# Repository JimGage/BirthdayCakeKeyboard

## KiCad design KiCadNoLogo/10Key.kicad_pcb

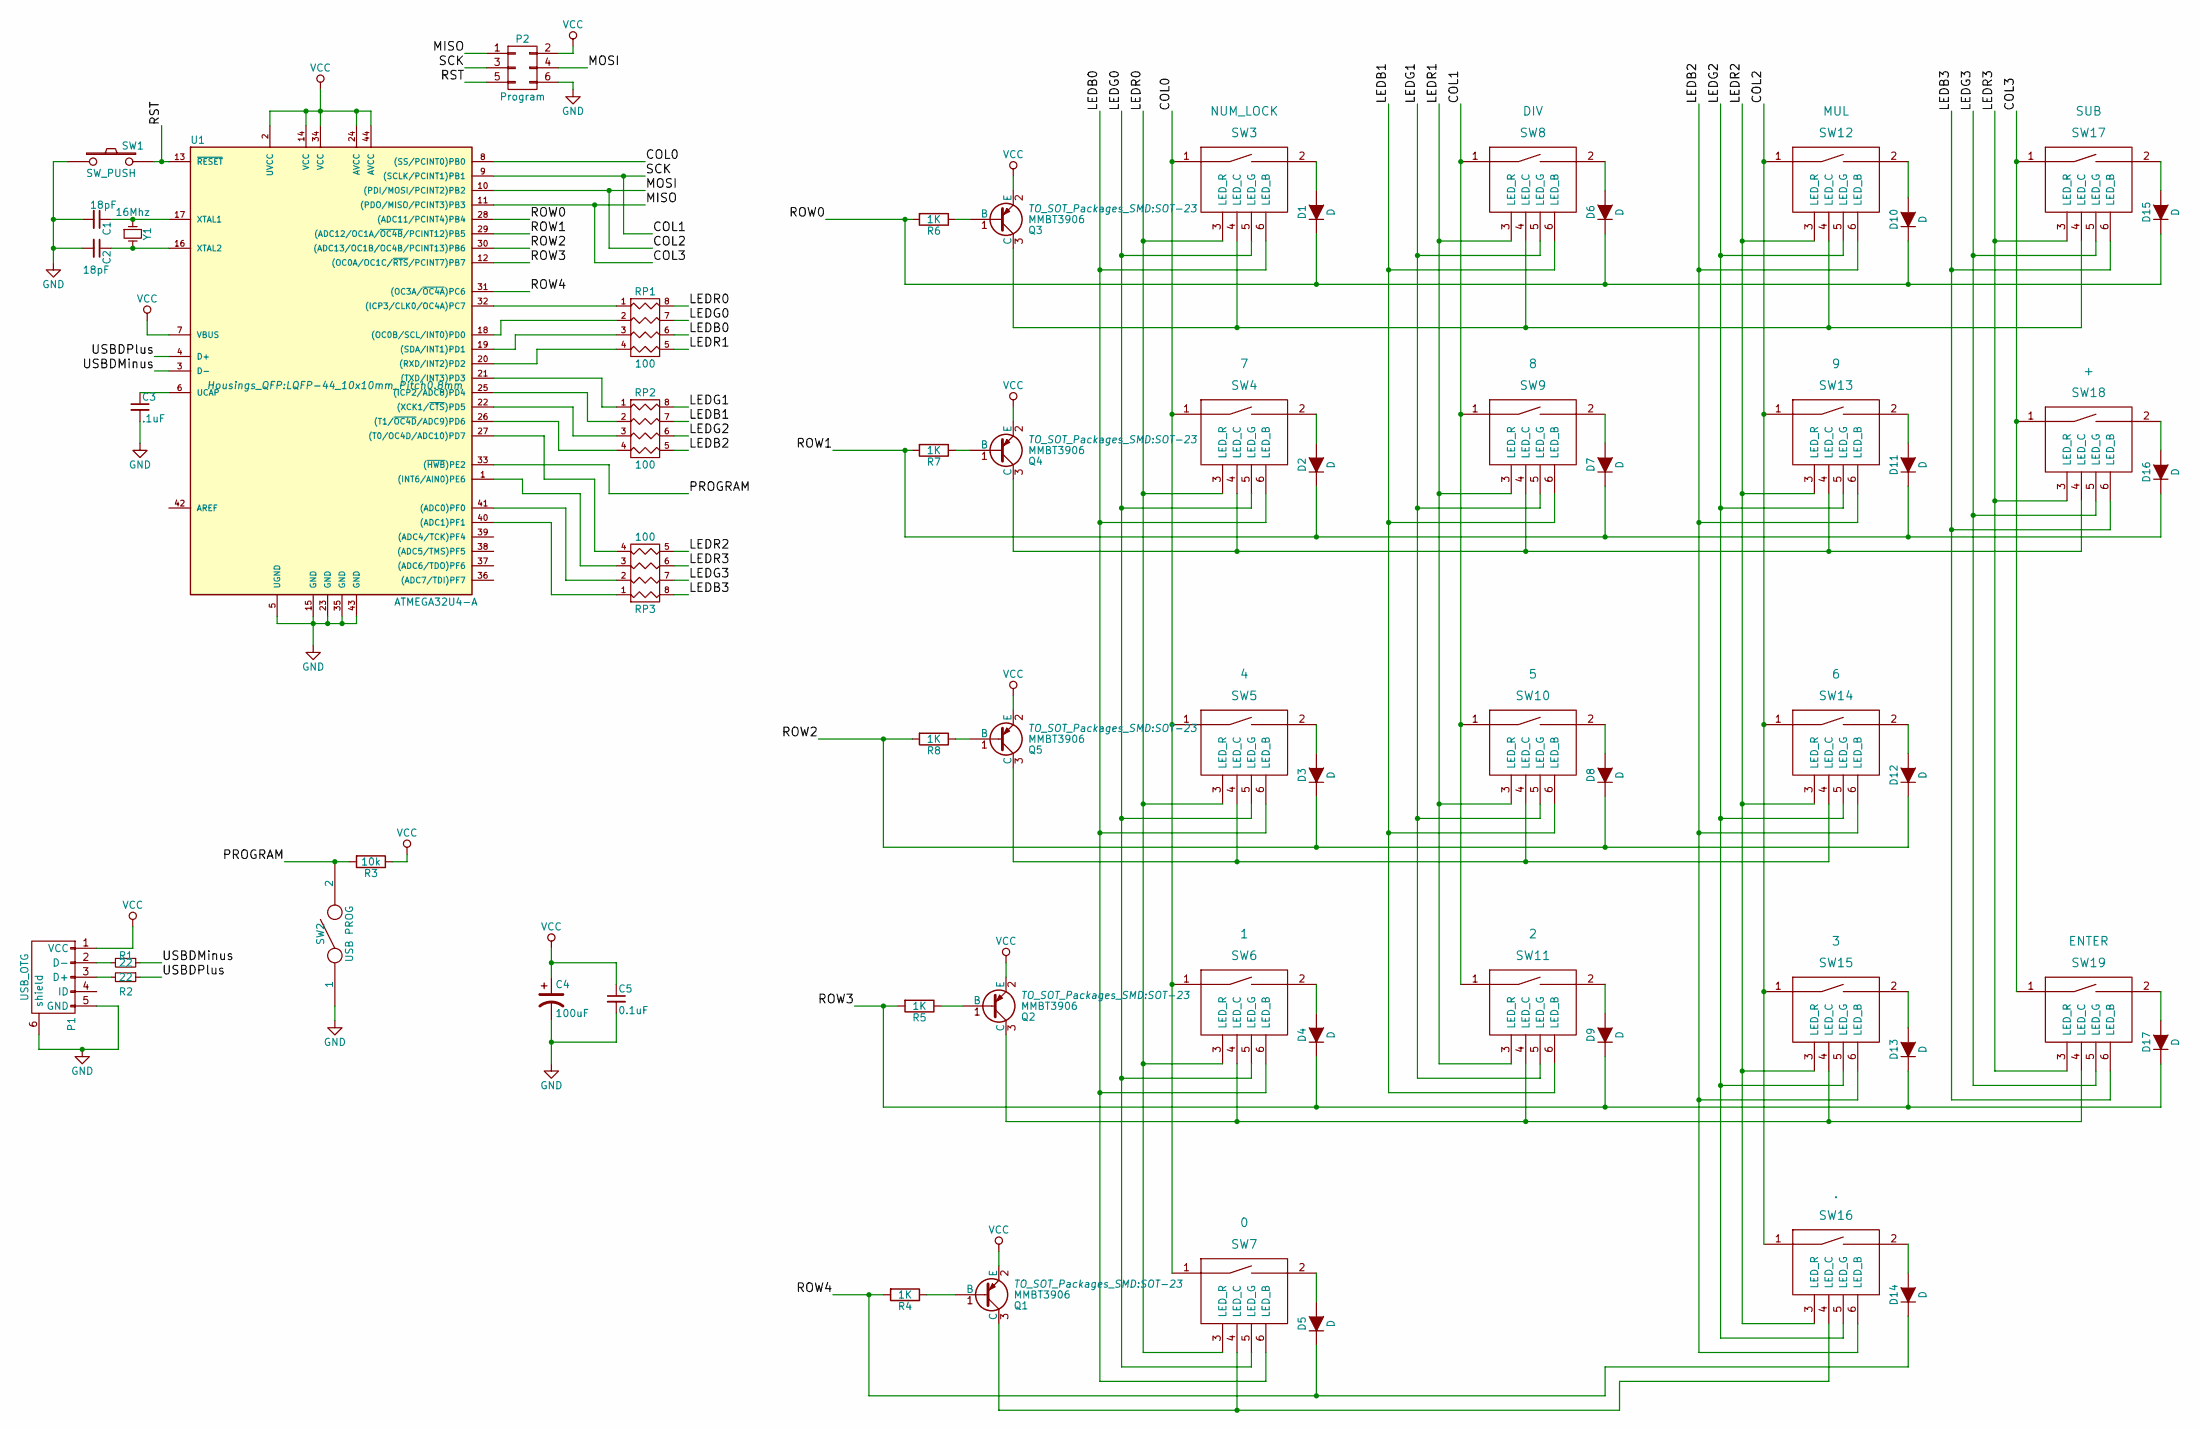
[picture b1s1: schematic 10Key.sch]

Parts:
C1, C2: 18pF; C_0603_HandSoldering
C3: .1uF; C_0603_HandSoldering
C4: 100uF; SMD-1206_Pol
C5: 0.1uF; C_0603_HandSoldering
D1, D2, D3, D4, D5, D6, D7, D8, D9, D10, D11, D12, D13, D14, D15, D16, D17: D; MiniMELF_Standard
P1: USB_OTG; USB_Micro-B
P2: Program; Pin_Header_Straight_2x03
Q1, Q2, Q3, Q4, Q5: MMBT3906; SOT-23
R1, R2: 22; R_0603_HandSoldering
R3: 10k; R_0603_HandSoldering
R4, R5, R6, R7, R8: 1K; R_0603_HandSoldering
RP1, RP2, RP3: 100; R_Array_Convex_4x1206
SW1: SW_PUSH; SW_SPST_EVQQ2
SW2: USB PROG; SW_SP3T_PCM13
SW3: NUM_LOCK; Zealios_Cherry_MX
SW4: 7; Zealios_Cherry_MX
SW5: 4; Zealios_Cherry_MX
SW6: 1; Zealios_Cherry_MX
SW7: 0; Zealios_Cherry_MX
SW8: DIV; Zealios_Cherry_MX
SW9: 8; Zealios_Cherry_MX
SW10: 5; Zealios_Cherry_MX
SW11: 2; Zealios_Cherry_MX
SW12: MUL; Zealios_Cherry_MX
SW13: 9; Zealios_Cherry_MX
SW14: 6; Zealios_Cherry_MX
SW15: 3; Zealios_Cherry_MX
SW16: .; Zealios_Cherry_MX
SW17: SUB; Zealios_Cherry_MX
SW18: +; Zealios_Cherry_MX
SW19: ENTER; Zealios_Cherry_MX
U1: ATMEGA32U4-A; LQFP-44_10x10mm_Pitch0.8mm
Y1: 16Mhz; Q_49U3HMS

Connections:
/COL0: SW3.1, SW4.1, SW5.1, SW6.1, SW7.1, U1.8 ((SS/PCINT0)PB0)
/COL1: P2.3, SW8.1, SW9.1, SW10.1, SW11.1, U1.9 ((SCLK/PCINT1)PB1)
/COL2: P2.4, SW12.1, SW13.1, SW14.1, SW15.1, SW16.1, U1.10 ((PDI/MOSI/PCINT2)PB2)
/COL3: P2.1, SW17.1, SW18.1, SW19.1, U1.11 ((PDO/MISO/PCINT3)PB3)
/LEDB0: RP1.6 (R3), SW3.6 (LED_B), SW4.6 (LED_B), SW5.6 (LED_B), SW6.6 (LED_B), SW7.6 (LED_B)
/LEDB1: RP2.7 (R2), SW8.6 (LED_B), SW9.6 (LED_B), SW10.6 (LED_B), SW11.6 (LED_B)
/LEDB2: RP2.5 (R4), SW12.6 (LED_B), SW13.6 (LED_B), SW14.6 (LED_B), SW15.6 (LED_B), SW16.6 (LED_B)
/LEDB3: RP3.8 (R1), SW17.6 (LED_B), SW18.6 (LED_B), SW19.6 (LED_B)
/LEDG0: RP1.7 (R2), SW3.5 (LED_G), SW4.5 (LED_G), SW5.5 (LED_G), SW6.5 (LED_G), SW7.5 (LED_G)
/LEDG1: RP2.8 (R1), SW8.5 (LED_G), SW9.5 (LED_G), SW10.5 (LED_G), SW11.5 (LED_G)
/LEDG2: RP2.6 (R3), SW12.5 (LED_G), SW13.5 (LED_G), SW14.5 (LED_G), SW15.5 (LED_G), SW16.5 (LED_G)
/LEDG3: RP3.7 (R2), SW17.5 (LED_G), SW18.5 (LED_G), SW19.5 (LED_G)
/LEDR0: RP1.8 (R1), SW3.3 (LED_R), SW4.3 (LED_R), SW5.3 (LED_R), SW6.3 (LED_R), SW7.3 (LED_R)
/LEDR1: RP1.5 (R4), SW8.3 (LED_R), SW9.3 (LED_R), SW10.3 (LED_R), SW11.3 (LED_R)
/LEDR2: RP3.5 (R4), SW12.3 (LED_R), SW13.3 (LED_R), SW14.3 (LED_R), SW15.3 (LED_R), SW16.3 (LED_R)
/LEDR3: RP3.6 (R3), SW17.3 (LED_R), SW18.3 (LED_R), SW19.3 (LED_R)
/PROGRAM: R3.2, SW2.2, U1.33 ((~HWB~)PE2)
/ROW0: D1.1 (K), D6.1 (K), D10.1 (K), D15.1 (K), R6.2, U1.28 ((ADC11/PCINT4)PB4)
/ROW1: D2.1 (K), D7.1 (K), D11.1 (K), D16.1 (K), R7.2, U1.29 ((ADC12/OC1A/~OC4B~/PCINT12)PB5)
/ROW2: D3.1 (K), D8.1 (K), D12.1 (K), R8.2, U1.30 ((ADC13/OC1B/OC4B/PCINT13)PB6)
/ROW3: D4.1 (K), D9.1 (K), D13.1 (K), D17.1 (K), R5.2, U1.12 ((OC0A/OC1C/~RTS~/PCINT7)PB7)
/ROW4: D5.1 (K), D14.1 (K), R4.2, U1.31 ((OC3A/~OC4A~)PC6)
/RST: P2.5, SW1.2, U1.13 (~RESET~)
/USBDMinus: R1.1, U1.3 (D-)
/USBDPlus: R2.1, U1.4 (D+)
GND: C1.2, C2.2, C3.2, C4.2, C5.2, P1.5 (GND), P1.6 (shield), P2.6, SW1.1, SW2.1, U1.5 (UGND), U1.15 (GND), U1.23 (GND), U1.35 (GND), U1.43 (GND)
unnamed: C1.1, U1.17 (XTAL1), Y1.1
unnamed: C2.1, U1.16 (XTAL2), Y1.2
unnamed: C3.1, U1.6 (UCAP)
unnamed: D1.2 (A), SW3.2
unnamed: D2.2 (A), SW4.2
unnamed: D3.2 (A), SW5.2
unnamed: D4.2 (A), SW6.2
unnamed: D5.2 (A), SW7.2
unnamed: D6.2 (A), SW8.2
unnamed: D7.2 (A), SW9.2
unnamed: D8.2 (A), SW10.2
unnamed: D9.2 (A), SW11.2
unnamed: D10.2 (A), SW12.2
unnamed: D11.2 (A), SW13.2
unnamed: D12.2 (A), SW14.2
unnamed: D13.2 (A), SW15.2
unnamed: D14.2 (A), SW16.2
unnamed: D15.2 (A), SW17.2
unnamed: D16.2 (A), SW18.2
unnamed: D17.2 (A), SW19.2
unnamed: P1.2 (D-), R1.2
unnamed: P1.3 (D+), R2.2
unnamed: Q1.1 (B), R4.1
unnamed: Q1.3 (C), SW7.4 (LED_C), SW16.4 (LED_C)
unnamed: Q2.1 (B), R5.1
unnamed: Q2.3 (C), SW6.4 (LED_C), SW11.4 (LED_C), SW15.4 (LED_C), SW19.4 (LED_C)
unnamed: Q3.1 (B), R6.1
unnamed: Q3.3 (C), SW3.4 (LED_C), SW8.4 (LED_C), SW12.4 (LED_C), SW17.4 (LED_C)
unnamed: Q4.1 (B), R7.1
unnamed: Q4.3 (C), SW4.4 (LED_C), SW9.4 (LED_C), SW13.4 (LED_C), SW18.4 (LED_C)
unnamed: Q5.1 (B), R8.1
unnamed: Q5.3 (C), SW5.4 (LED_C), SW10.4 (LED_C), SW14.4 (LED_C)
unnamed: RP1.1, U1.32 ((ICP3/CLK0/OC4A)PC7)
unnamed: RP1.2, U1.18 ((OC0B/SCL/INT0)PD0)
unnamed: RP1.3, U1.19 ((SDA/INT1)PD1)
unnamed: RP1.4, U1.20 ((RXD/INT2)PD2)
unnamed: RP2.1, U1.21 ((TXD/INT3)PD3)
unnamed: RP2.2, U1.25 ((ICP2/ADC8)PD4)
unnamed: RP2.3, U1.22 ((XCK1/~CTS~)PD5)
unnamed: RP2.4, U1.26 ((T1/~OC4D~/ADC9)PD6)
unnamed: RP3.1, U1.40 ((ADC1)PF1)
unnamed: RP3.2, U1.41 ((ADC0)PF0)
unnamed: RP3.3, U1.1 ((INT6/AIN0)PE6)
unnamed: RP3.4, U1.27 ((T0/OC4D/ADC10)PD7)
VCC: C4.1, C5.1, P1.1 (VCC), P2.2, Q1.2 (E), Q2.2 (E), Q3.2 (E), Q4.2 (E), Q5.2 (E), R3.1, U1.2 (UVCC), U1.7 (VBUS), U1.14 (VCC), U1.24 (AVCC), U1.34 (VCC), U1.44 (AVCC)

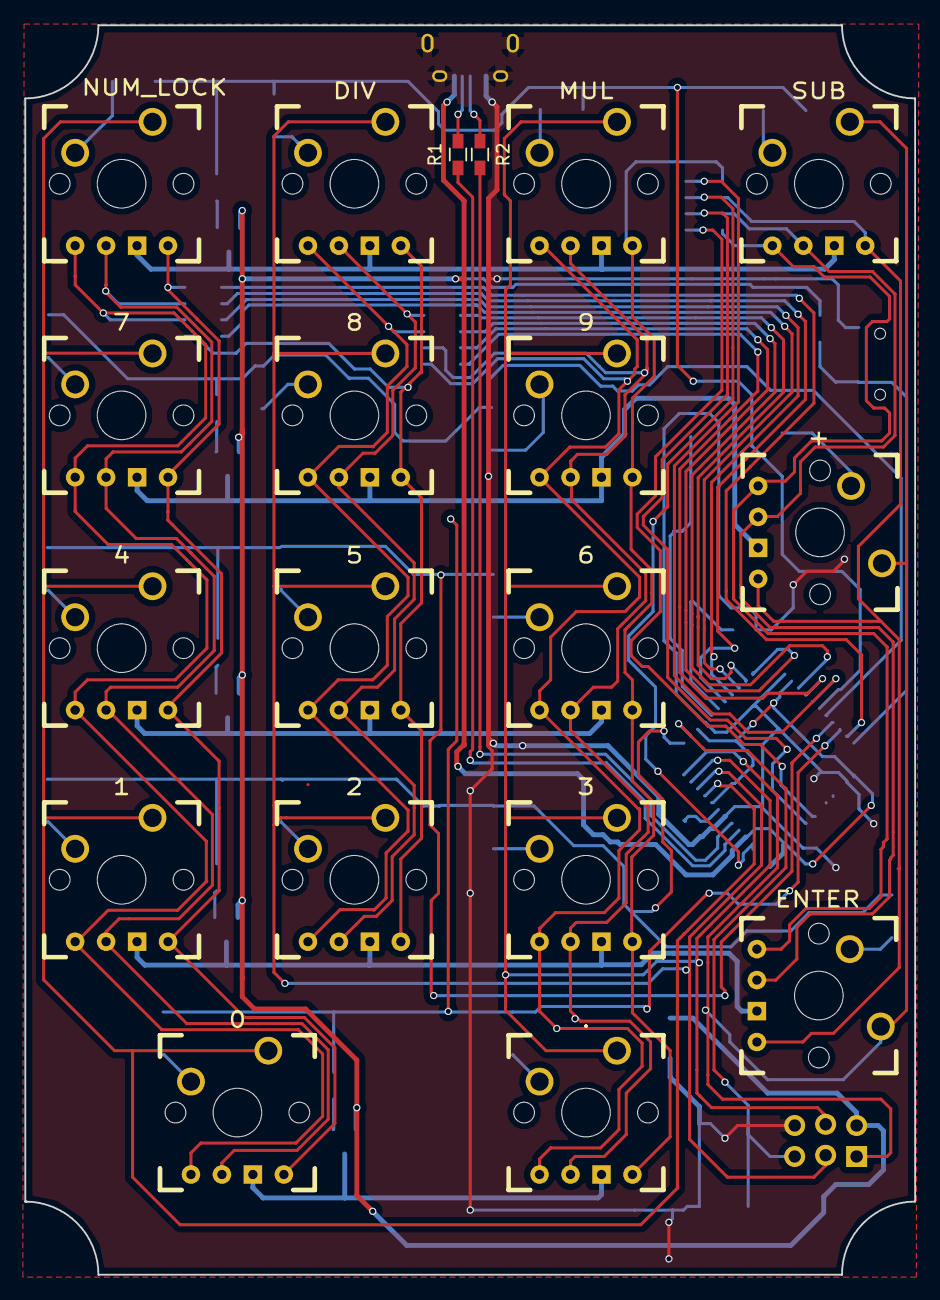
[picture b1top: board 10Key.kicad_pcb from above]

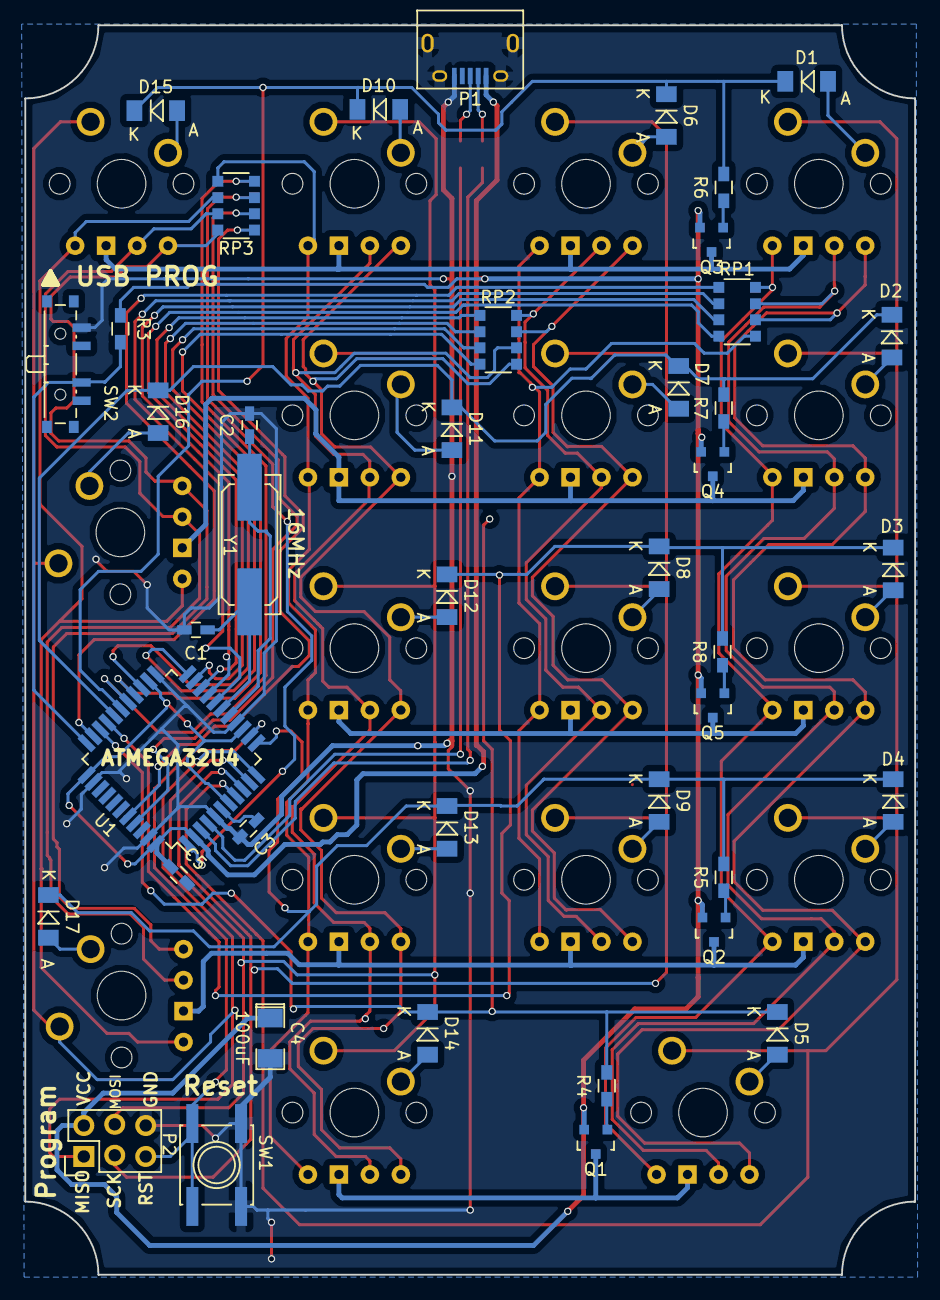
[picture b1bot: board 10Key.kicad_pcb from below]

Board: 2 copper layers, 73.0 x 102.5 mm, 61 parts (42 on the bottom side), 71 nets.

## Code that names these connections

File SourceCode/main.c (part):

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
// High is off, Low is on

// RGB 0 = PD2, PD3, PD4
// RGB 1 = PD5, PD6, PD7
// RGB 2 = PE6, PF0, PF1
// RGB 3 = PF4, PF5, PF6

// RGB 0 = PC7 PD0 PD1
// RGB 1 = PD2 PD3 PD4
// RGB 2 = PD6 PD7 PD5
// RGB 3 = PE6 PF0 PF1

//----------------------------------------------------------------------------
// set the first column of LEDs 
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void SetOutputPinsForRow( uint8_t const row )
{
#if 0
   // ROW0 = PB7, ROW1 = PC6, ROW2 = PC7, ROW3 = PD0, ROW4 = PD1
   // COL0 = PB0, COL1 = PB4, COL2 = PB5, COL3 = PB6

   // Each row is held low to drive it and high to clear it

   PORTB |= 0x80;  // clear pb7
   PORTC |= (0x80 | 0x40); // clear pc6 and pc7
   PORTD |= (0x01 | 0x02);

   switch (row)
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      break;
   }
#endif
   // ROW0 = PB4, ROW1 = PB5, ROW2 = PB6, ROW3 = PB7, ROW4 = PC6

   PORTB |= 0xF0;
   PORTC |= 0x40;
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
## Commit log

2016-08-02 Adding a version of the PCB with no logo.
2016-08-02 Created parts list
    This is currently my best guess on parts used. A few parts I pulled from my parts drawer had no labels.
2016-08-02 Added atmega to the parts list.
2016-08-09 * Added extra capacitance * Added current limiting resistors * Moved connections off of the jtag pins so that an external programmer * will not be needed to set fuses.
2016-09-18 Updated no logo pcb with current limiting resistors.
2017-01-08 Added current limiting resistors.
    A bunch of clean up. Added current limiting resistors. Moved a number of connections off of the JTAG pins so that they don't need to have fuses reconfigured.
2017-01-08 Reconfigured pins.
    Some pins have been moved so that they don't rely on the JTAG pins which require the fuses to be updated. Can now be updated through the initial firmware updater.
2017-01-08 Added top bezel
    Added a bezel for the top and made the box a little bit deeper.
